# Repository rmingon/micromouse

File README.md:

# MICRO MOUSE Project

### 3d view

### pcb view

### schematic view

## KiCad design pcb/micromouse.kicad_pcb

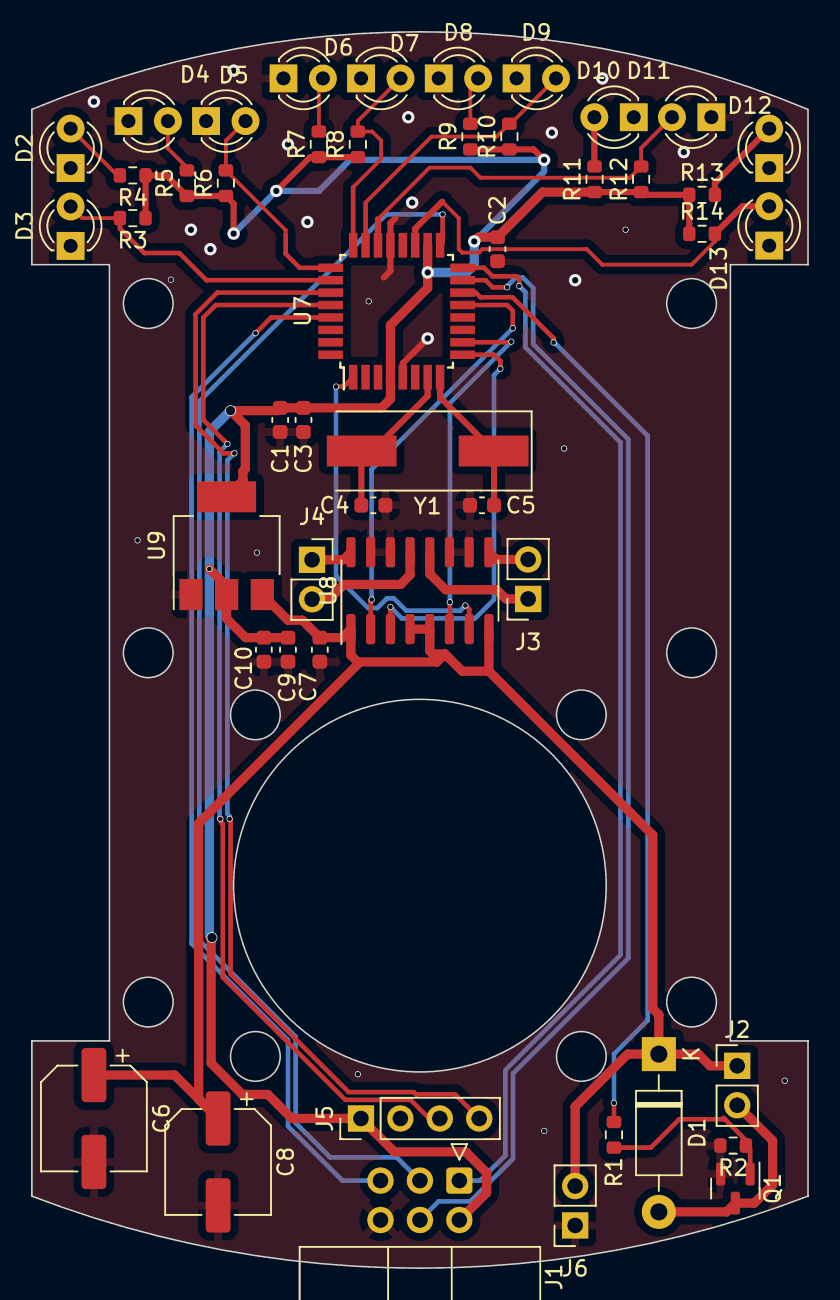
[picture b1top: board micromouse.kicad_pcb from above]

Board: 2 copper layers, 50.0 x 79.6 mm, 48 parts (0 on the bottom side), 34 nets.

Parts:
C1, C2, C4, C5, C7, C9, C10: 10u; C_0603_1608Metric
C3: 1u; C_0603_1608Metric
C6, C8: C_Polarized_Small; CP_Elec_6.3x4.9
D1: 1N5819; D_DO-41_SOD81_P10.16mm_Horizontal
D2, D3, D4, D5, D6, D7, D8, D9, D10, D11, D12, D13: TSAL4400; LED_D3.0mm_IRBlack
J1: AVR-ISP-6; IDC-Header_2x03_P2.54mm_Horizontal
J2: Conn_01x02; PinHeader_1x02_P2.54mm_Vertical
J3, J4, J6: Conn_01x02; PinSocket_1x02_P2.54mm_Vertical
J5: Conn_01x04; PinHeader_1x04_P2.54mm_Vertical
Q1: Si2319CDS; SOT-23
R1, R2, R3, R4, R5, R6, R7, R8, R9, R10, R11, R12, R13, R14: R_Small; R_0603_1608Metric
U7: ATmega328PB-A; TQFP-32_7x7mm_P0.8mm
U8: MX1508; SOIC-16_3.9x9.9mm_P1.27mm
U9: LM317_SOT-223; SOT-223-3_TabPin2
Y1: Crystal; Crystal_SMD_HC49-SD

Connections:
+3.3V: C1.1, C2.1, C3.1, C9.1, C10.1, J1.2 (VCC), J5.1, R3.1, R4.1, R5.1, R6.1, R7.1, R8.1, R9.1, R10.1, R11.1, R12.1, R13.1, R14.1, U7.4 (VCC), U7.18 (AVCC), U9.2 (VO)
+BATT: C6.1, C7.1, C8.1, D1.1 (K), J2.1, J6.2, U8.1 (VCC1), U8.4 (VDD1), U8.5 (VCC2), U8.8 (VDD2), U9.3 (VI)
GND: C1.2, C2.2, C3.2, C4.2, C5.2, C6.2, C7.2, C8.2, C9.2, C10.2, D2.1 (K), D3.1 (K), D4.1 (K), D5.1 (K), D6.1 (K), D7.1 (K), D8.1 (K), D9.1 (K), D10.1 (K), D11.1 (K), D12.1 (K), D13.1 (K), J1.6 (GND), J5.2, J6.1, Q1.2 (S), R2.2, U7.5 (GND), U7.21 (GND), U8.10 (AGND2), U8.11 (PGND2), U8.14 (AGND1), U8.15 (PGND1), U9.1 (ADJ)
IR1: D3.2 (A), R3.2, U7.26 (PC3)
IR2: D5.2 (A), R6.2, U7.25 (PC2)
IR3: D7.2 (A), R8.2, U7.24 (PC1)
IR4: D9.2 (A), R10.2, U7.23 (PC0)
IR5: D11.2 (A), R12.2, U7.22 (PE3)
IR6: D13.2 (A), R14.2, U7.19 (PE2)
MISO: J1.1 (MISO), U7.16 (PB4)
MOSI: J1.4 (MOSI), U7.15 (PB3)
MOTOR_1: R1.1, U7.14 (PB2)
MTR_L_1: U7.13 (PB1), U8.2 (INA1)
MTR_L_2: U7.9 (PD5), U8.3 (INB1)
MTR_R_1: U7.10 (PD6), U8.6 (INA2)
MTR_R_2: U7.1 (PD3), U8.7 (INB2)
unnamed: D1.2 (A), J2.2, Q1.3 (D)
unnamed: D2.2 (A), R4.2
unnamed: D4.2 (A), R5.2
unnamed: D6.2 (A), R7.2
unnamed: D8.2 (A), R9.2
unnamed: D10.2 (A), R11.2
unnamed: D12.2 (A), R13.2
unnamed: J3.1, U8.12 (OUTA2)
unnamed: J3.2, U8.9 (OUTB2)
unnamed: J4.1, U8.16 (OUTA1)
unnamed: J4.2, U8.13 (OUTB1)
unnamed: Q1.1 (G), R1.2, R2.1
RST: J1.5 (~RST), U7.29 (~RESET/PC6)
SCK: J1.3 (SCK), U7.17 (PB5)
SCL: J5.3, U7.28 (PC5)
SDA: J5.4, U7.27 (PC4)
XTAL1: C4.1, U7.7 (XTAL1/PB6), Y1.2
XTAL2: C5.1, U7.8 (XTAL2/PB7), Y1.1

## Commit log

2024-07-01 add ir sensor
2024-07-01 add mcu
2024-07-01 add program port
2024-07-01 wiring mcu program port
2024-07-01 add motor control
2024-07-01 wiring mcu
2024-07-02 add fan control
2024-07-02 add motor + fan
2024-07-02 add IR 3d + pin i2c screen
2024-07-02 remake IR wiring
2024-07-02 update link
2024-07-03 add pictures
2024-07-03 add readme
2024-07-10 update output
2024-07-24 first commit code
2024-07-29 update ir sensor
2024-07-29 leds placed
2024-07-29 leds resistor placed
2024-07-29 finish wiring
2024-07-29 update views
2024-07-30 update plot settings
2025-03-28 Update README.md
    add videos link
